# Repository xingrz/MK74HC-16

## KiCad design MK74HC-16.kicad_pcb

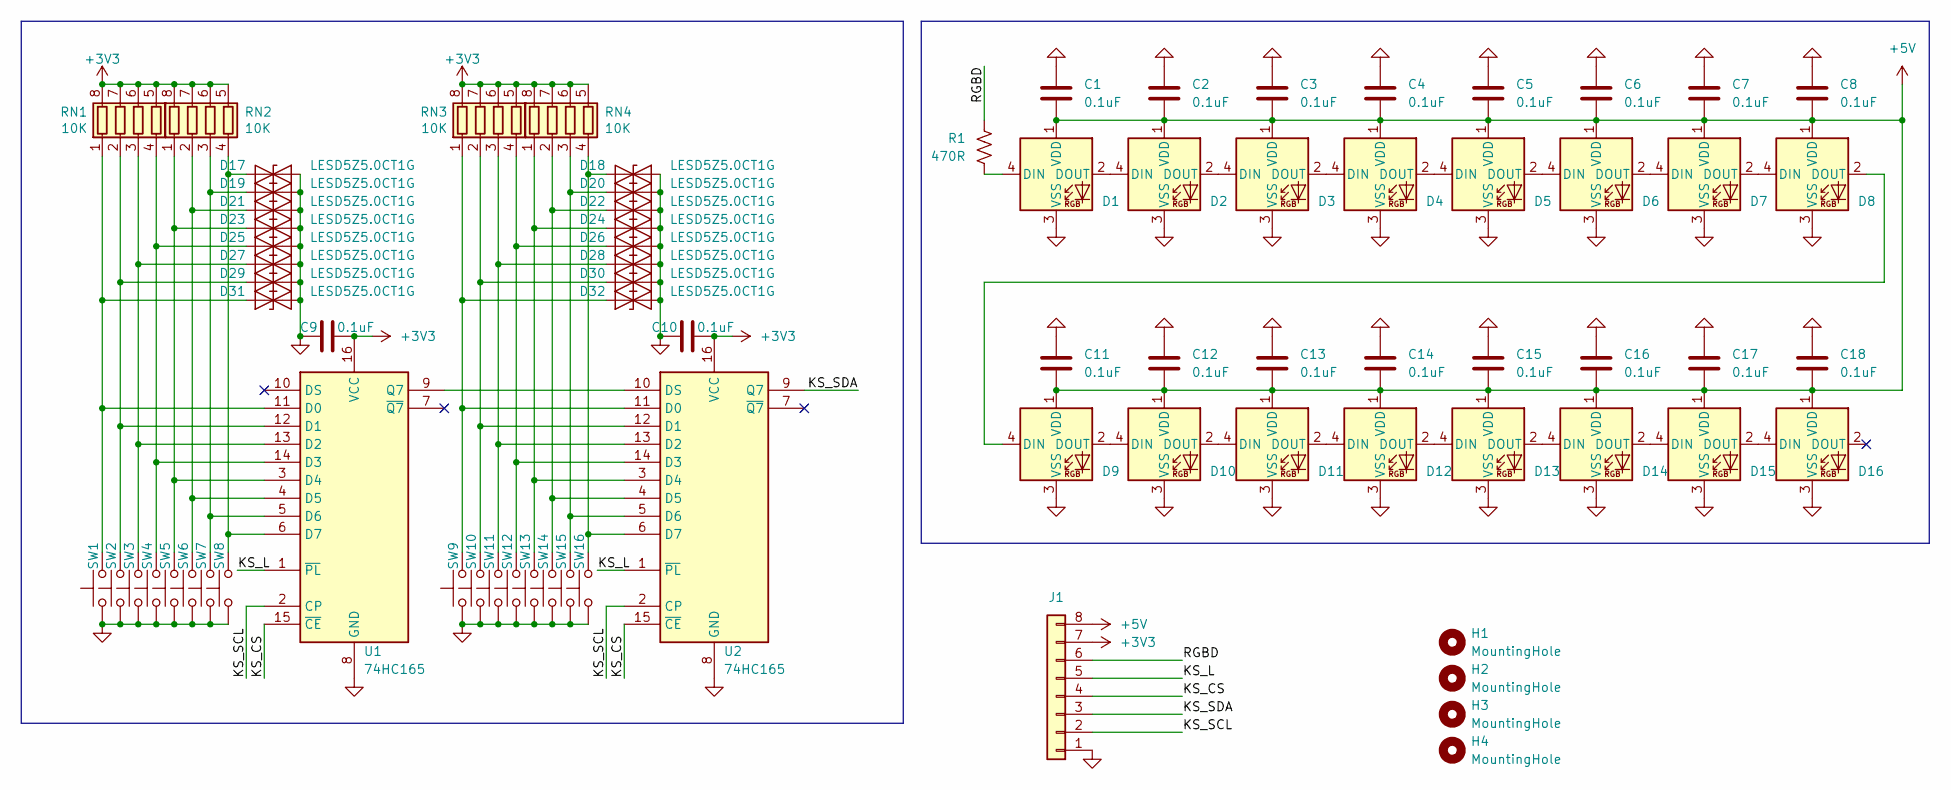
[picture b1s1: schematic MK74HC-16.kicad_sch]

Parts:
C1, C2, C3, C4, C5, C6, C7, C8, C9, C10, C11, C12, C13, C14, C15, C16, C17, C18: 0.1uF; C_0402_1005Metric; PartNumber C1525
D1, D2, D3, D4, D5, D6, D7, D8, D9, D10, D11, D12, D13, D14, D15, D16: WS2812B; TONYU_DY-S352818; PartNumber C524051
D17, D18, D19, D20, D21, D22, D23, D24, D25, D26, D27, D28, D29, D30, D31, D32: LESD5Z5.0CT1G; D_SOD-523; PartNumber C136167
H1, H2, H3, H4: MountingHole; MountingHole_2.2mm_M2
J1: Conn_01x08; PinHeader_1x08_P2.54mm_Horizontal
R1: 470R; R_0402_1005Metric; PartNumber C25117
RN1, RN2, RN3, RN4: 10K; R_Array_Convex_4x0402; PartNumber C25725
SW1, SW2, SW3, SW4, SW5, SW6, SW7, SW8, SW9, SW10, SW11, SW12, SW13, SW14, SW15, SW16: CPG151101S11; SW_Hotswap_Kailh_MX_1.00u; PartNumber C2803348
U1, U2: 74HC165; SOIC-16_3.9x9.9mm_P1.27mm; PartNumber C5613

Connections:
+3V3: C9.1, C10.1, J1.7, RN1.5 (R4.2), RN1.6 (R3.2), RN1.7 (R2.2), RN1.8 (R1.2), RN2.5 (R4.2), RN2.6 (R3.2), RN2.7 (R2.2), RN2.8 (R1.2), RN3.5 (R4.2), RN3.6 (R3.2), RN3.7 (R2.2), RN3.8 (R1.2), RN4.5 (R4.2), RN4.6 (R3.2), RN4.7 (R2.2), RN4.8 (R1.2), U1.16 (VCC), U2.16 (VCC)
+5V: C1.1, C2.1, C3.1, C4.1, C5.1, C6.1, C7.1, C8.1, C11.1, C12.1, C13.1, C14.1, C15.1, C16.1, C17.1, C18.1, D1.1 (VDD), D2.1 (VDD), D3.1 (VDD), D4.1 (VDD), D5.1 (VDD), D6.1 (VDD), D7.1 (VDD), D8.1 (VDD), D9.1 (VDD), D10.1 (VDD), D11.1 (VDD), D12.1 (VDD), D13.1 (VDD), D14.1 (VDD), D15.1 (VDD), D16.1 (VDD), J1.8
/KS_CS: J1.4, U1.15 (~CE), U2.15 (~CE)
/KS_L: J1.5, U1.1 (~PL), U2.1 (~PL)
/KS_SCL: J1.2, U1.2 (CP), U2.2 (CP)
/KS_SDA: J1.3, U2.9 (Q7)
/RGBD: J1.6, R1.1
GND: C1.2, C2.2, C3.2, C4.2, C5.2, C6.2, C7.2, C8.2, C9.2, C10.2, C11.2, C12.2, C13.2, C14.2, C15.2, C16.2, C17.2, C18.2, D1.3 (VSS), D2.3 (VSS), D3.3 (VSS), D4.3 (VSS), D5.3 (VSS), D6.3 (VSS), D7.3 (VSS), D8.3 (VSS), D9.3 (VSS), D10.3 (VSS), D11.3 (VSS), D12.3 (VSS), D13.3 (VSS), D14.3 (VSS), D15.3 (VSS), D16.3 (VSS), D17.2 (A2), D18.2 (A2), D19.2 (A2), D20.2 (A2), D21.2 (A2), D22.2 (A2), D23.2 (A2), D24.2 (A2), D25.2 (A2), D26.2 (A2), D27.2 (A2), D28.2 (A2), D29.2 (A2), D30.2 (A2), D31.2 (A2), D32.2 (A2), J1.1, SW1.1, SW2.1, SW3.1, SW4.1, SW5.1, SW6.1, SW7.1, SW8.1, SW9.1, SW10.1, SW11.1, SW12.1, SW13.1, SW14.1, SW15.1, SW16.1, U1.8 (GND), U2.8 (GND)
unnamed: D1.2 (DOUT), D2.4 (DIN)
unnamed: D1.4 (DIN), R1.2
unnamed: D2.2 (DOUT), D3.4 (DIN)
unnamed: D3.2 (DOUT), D4.4 (DIN)
unnamed: D4.2 (DOUT), D5.4 (DIN)
unnamed: D5.2 (DOUT), D6.4 (DIN)
unnamed: D6.2 (DOUT), D7.4 (DIN)
unnamed: D7.2 (DOUT), D8.4 (DIN)
unnamed: D8.2 (DOUT), D9.4 (DIN)
unnamed: D10.2 (DOUT), D11.4 (DIN)
unnamed: D9.2 (DOUT), D10.4 (DIN)
unnamed: D11.2 (DOUT), D12.4 (DIN)
unnamed: D12.2 (DOUT), D13.4 (DIN)
unnamed: D13.2 (DOUT), D14.4 (DIN)
unnamed: D14.2 (DOUT), D15.4 (DIN)
unnamed: D15.2 (DOUT), D16.4 (DIN)
unnamed: D17.1 (A1), RN2.4 (R4.1), SW8.2, U1.6 (D7)
unnamed: D18.1 (A1), RN4.4 (R4.1), SW16.2, U2.6 (D7)
unnamed: D19.1 (A1), RN2.3 (R3.1), SW7.2, U1.5 (D6)
unnamed: D20.1 (A1), RN4.3 (R3.1), SW15.2, U2.5 (D6)
unnamed: D21.1 (A1), RN2.2 (R2.1), SW6.2, U1.4 (D5)
unnamed: D22.1 (A1), RN4.2 (R2.1), SW14.2, U2.4 (D5)
unnamed: D23.1 (A1), RN2.1 (R1.1), SW5.2, U1.3 (D4)
unnamed: D24.1 (A1), RN4.1 (R1.1), SW13.2, U2.3 (D4)
unnamed: D25.1 (A1), RN1.4 (R4.1), SW4.2, U1.14 (D3)
unnamed: D26.1 (A1), RN3.4 (R4.1), SW12.2, U2.14 (D3)
unnamed: D27.1 (A1), RN1.3 (R3.1), SW3.2, U1.13 (D2)
unnamed: D28.1 (A1), RN3.3 (R3.1), SW11.2, U2.13 (D2)
unnamed: D29.1 (A1), RN1.2 (R2.1), SW2.2, U1.12 (D1)
unnamed: D30.1 (A1), RN3.2 (R2.1), SW10.2, U2.12 (D1)
unnamed: D31.1 (A1), RN1.1 (R1.1), SW1.2, U1.11 (D0)
unnamed: D32.1 (A1), RN3.1 (R1.1), SW9.2, U2.11 (D0)
unnamed: U1.9 (Q7), U2.10 (DS)

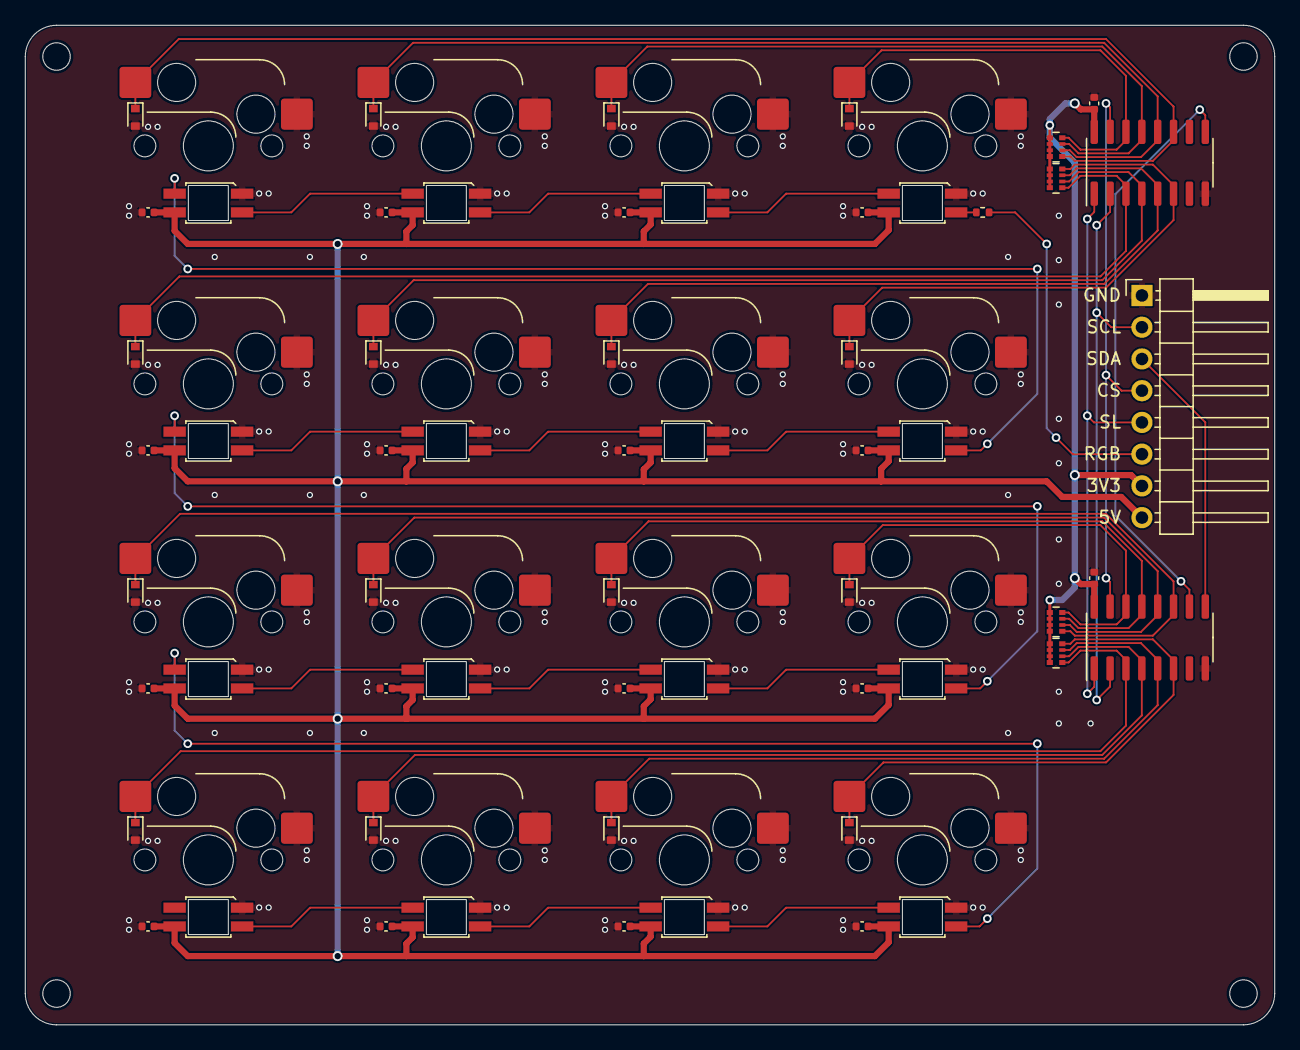
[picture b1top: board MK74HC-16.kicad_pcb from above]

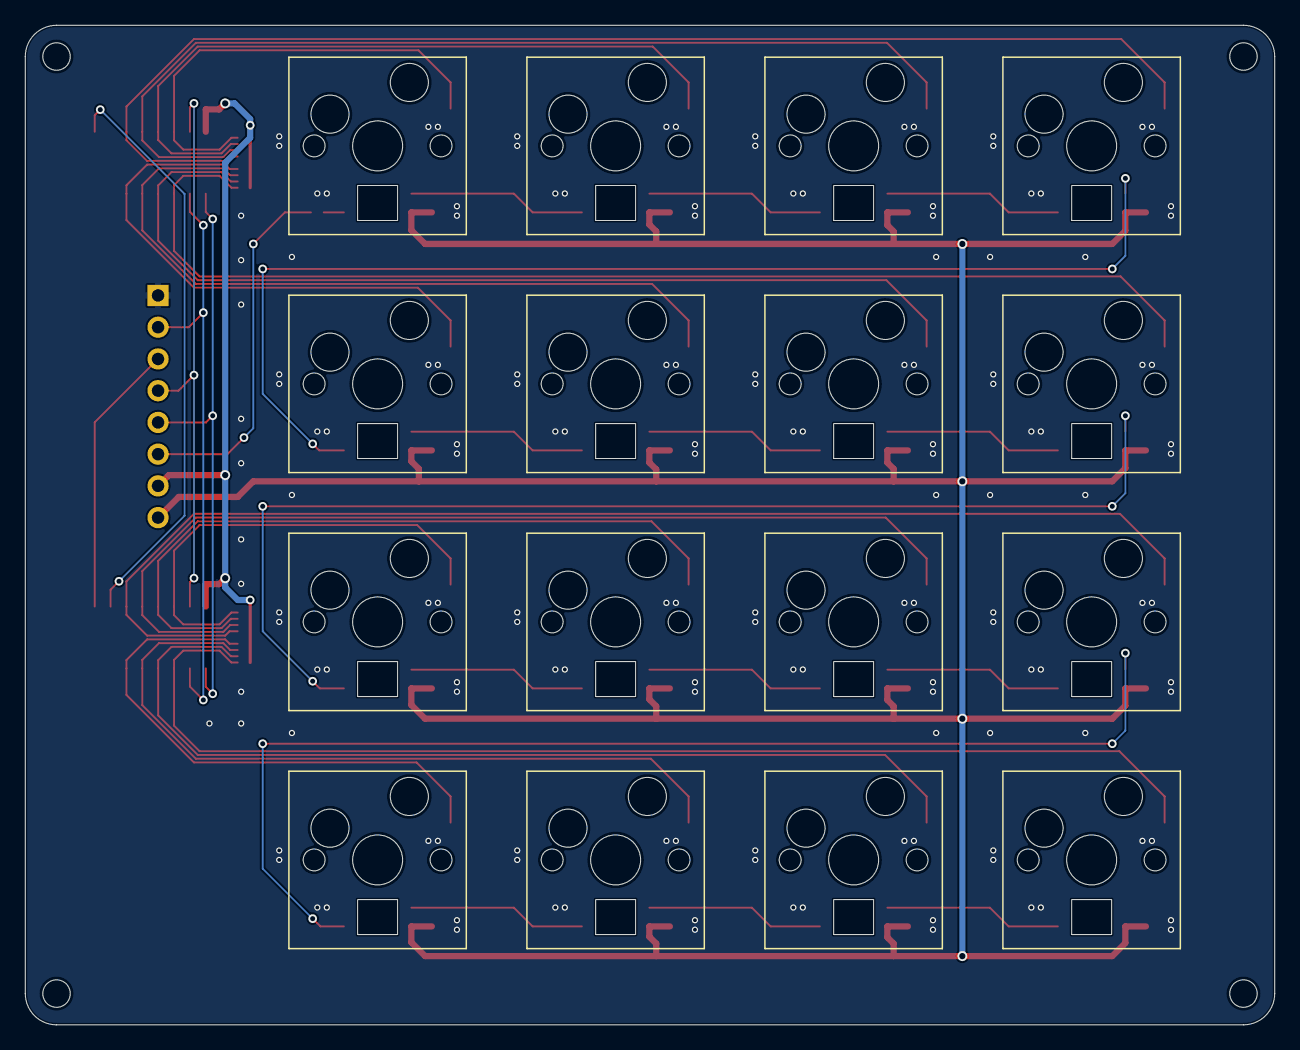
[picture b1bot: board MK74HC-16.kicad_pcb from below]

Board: 2 copper layers, 100.0 x 80.0 mm, 78 parts (16 on the bottom side), 41 nets.

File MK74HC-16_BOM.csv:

Manufacturer,Comment,Designator,Footprint,Quantity,PartNumber,Supplier
SAMSUNG,0.1uF,C1 C2 C3 C4 C5 C6 C7 C8 C9 C10 C11 C12 C13 C14 C15 C16 C17 C18,C_0402_1005Metric,18,C1525,JLC
UNI-ROYAL,470R,R1,R_0402_1005Metric,1,C25117,JLC
UNI-ROYAL,10K,RN1 RN2 RN3 RN4,R_Array_Convex_4x0402,4,C25725,JLC
Nexperia,74HC165,U1 U2,SOIC-16_3.9x9.9mm_P1.27mm,2,C5613,JLC
LRC,LESD5Z5.0CT1G,D17 D18 D19 D20 D21 D22 D23 D24 D25 D26 D27 D28 D29 D30 D31 D32,D_SOD-523,16,C136167,JLC-EXT
Kailh,CPG151101S11,SW1 SW2 SW3 SW4 SW5 SW6 SW7 SW8 SW9 SW10 SW11 SW12 SW13 SW14 SW15 SW16,SW_Hotswap_Kailh_MX_1.00u,16,C2803348,JLC-EXT
TONYU,WS2812B,D1 D2 D3 D4 D5 D6 D7 D8 D9 D10 D11 D12 D13 D14 D15 D16,TONYU_DY-S352818,16,C524051,JLC-EXT

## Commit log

2022-11-02 Output docs
2022-11-02 Make 16-keys evb
2022-11-02 Fix rotation
